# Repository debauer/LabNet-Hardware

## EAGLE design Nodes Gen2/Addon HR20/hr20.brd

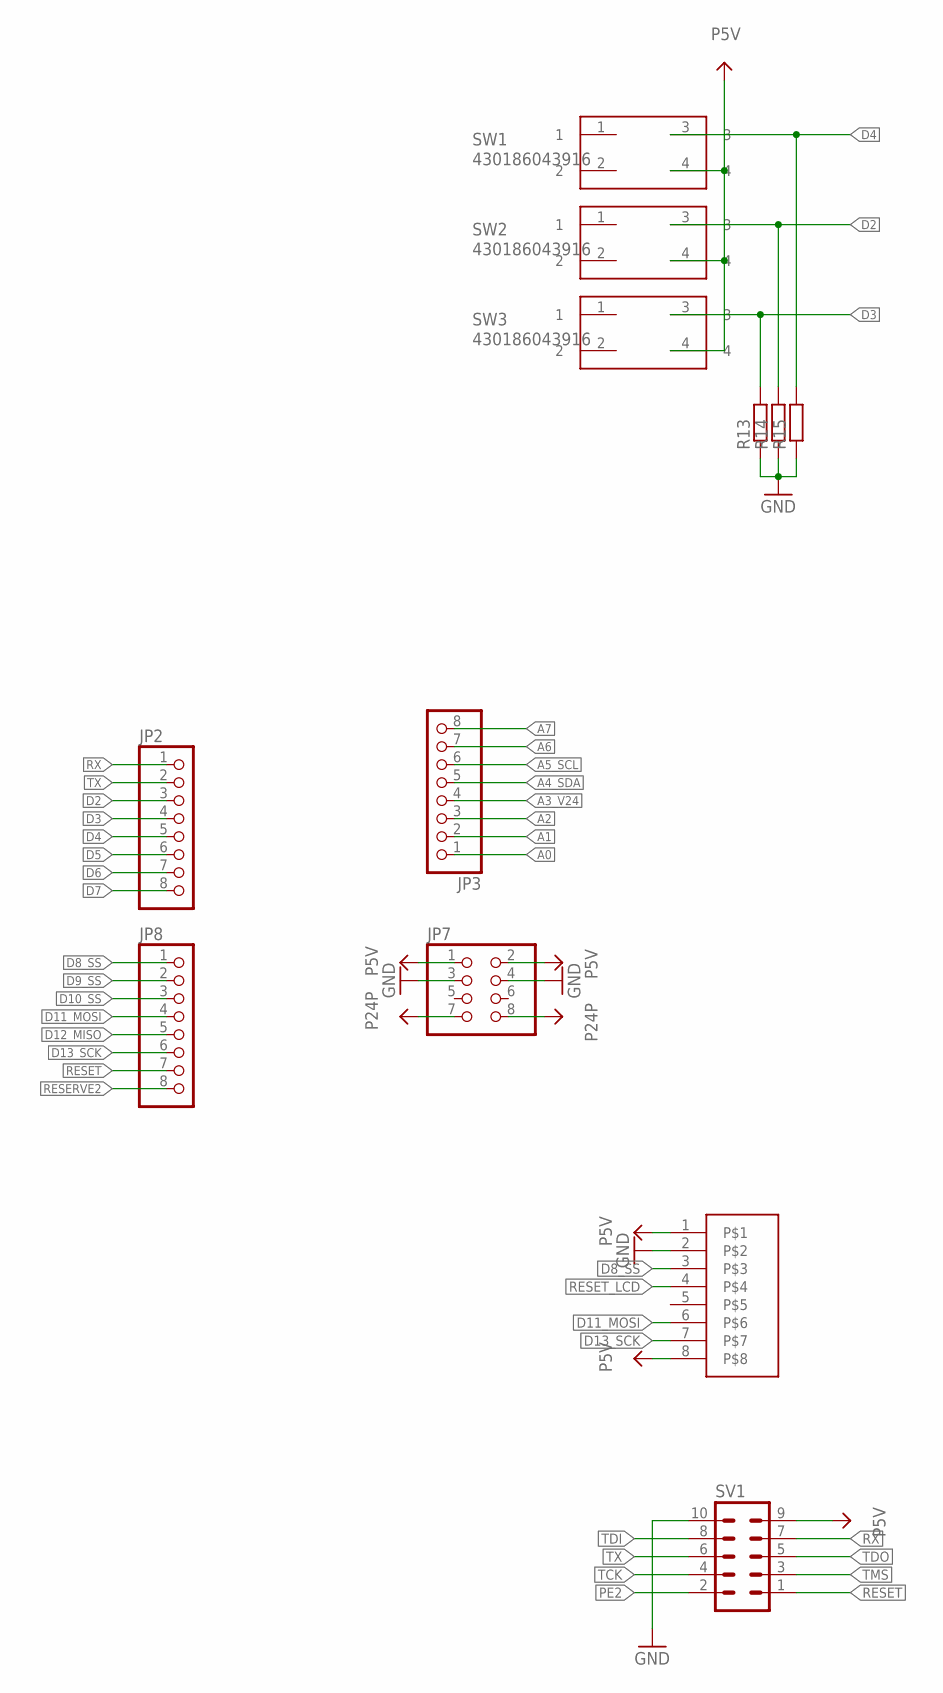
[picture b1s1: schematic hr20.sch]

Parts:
JP2, JP3, JP8: PINHD-1X8; 1X08
JP7: PINHD-2X4; 2X04
R13, R14, R15: R-EU_0207/10; 0207/10
SV1: ML10
SW1, SW2, SW3: 430186043916
U$2: 1.44-128X128

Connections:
A0: JP3.1
A1: JP3.2
A2: JP3.3
A3_V24: JP3.4
A4_SDA: JP3.5
A5_SCL: JP3.6
D2: JP2.3, R14.2, SW2.3
D3: JP2.4, R13.2, SW3.3
D4: JP2.5, R15.2, SW1.3
D5: JP2.6
D6: JP2.7
D7: JP2.8
D8_SS: JP8.1, U$2.3
D9_SS: JP8.2
D10_SS: JP8.3
D11_MOSI: JP8.4, U$2.6
D12_MISO: JP8.5
D13_SCK: JP8.6, U$2.7
GND: JP7.3, JP7.4, R13.1, R14.1, R15.1, SV1.10, U$2.2
P5V: JP7.1, JP7.2, SV1.9, SW1.4, SW2.4, SW3.4, U$2.1, U$2.8
P24P: JP7.7, JP7.8
PE2: SV1.2
RESERVE2: JP8.8
RESET: JP8.7, SV1.1
RESET_LCD: U$2.4
RX: JP2.1, SV1.7
TCK: SV1.4
TDI: SV1.8
TDO: SV1.5
TMS: SV1.3
TX: JP2.2, SV1.6

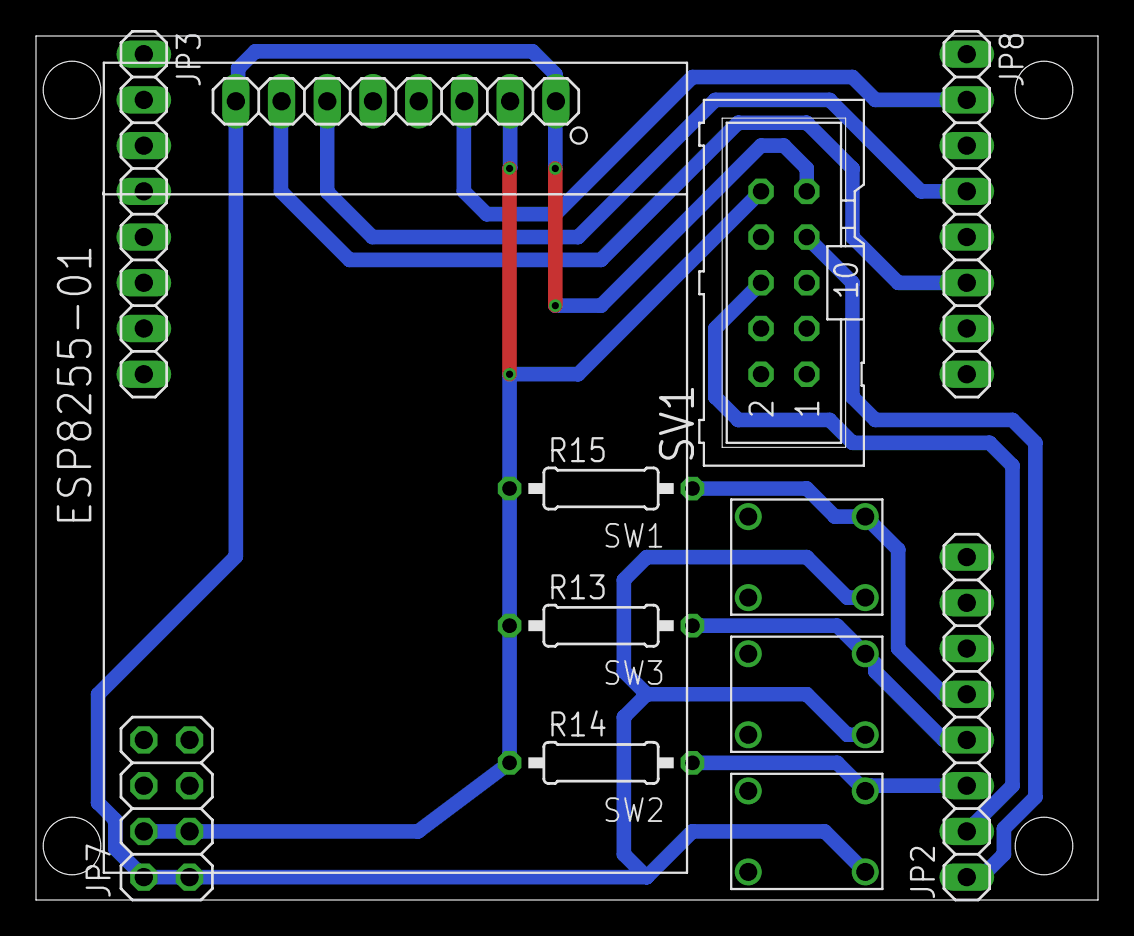
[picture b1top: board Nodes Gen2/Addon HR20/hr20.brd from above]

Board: 2 copper layers, 59.0 x 48.0 mm, 12 parts (0 on the bottom side), 12 nets.

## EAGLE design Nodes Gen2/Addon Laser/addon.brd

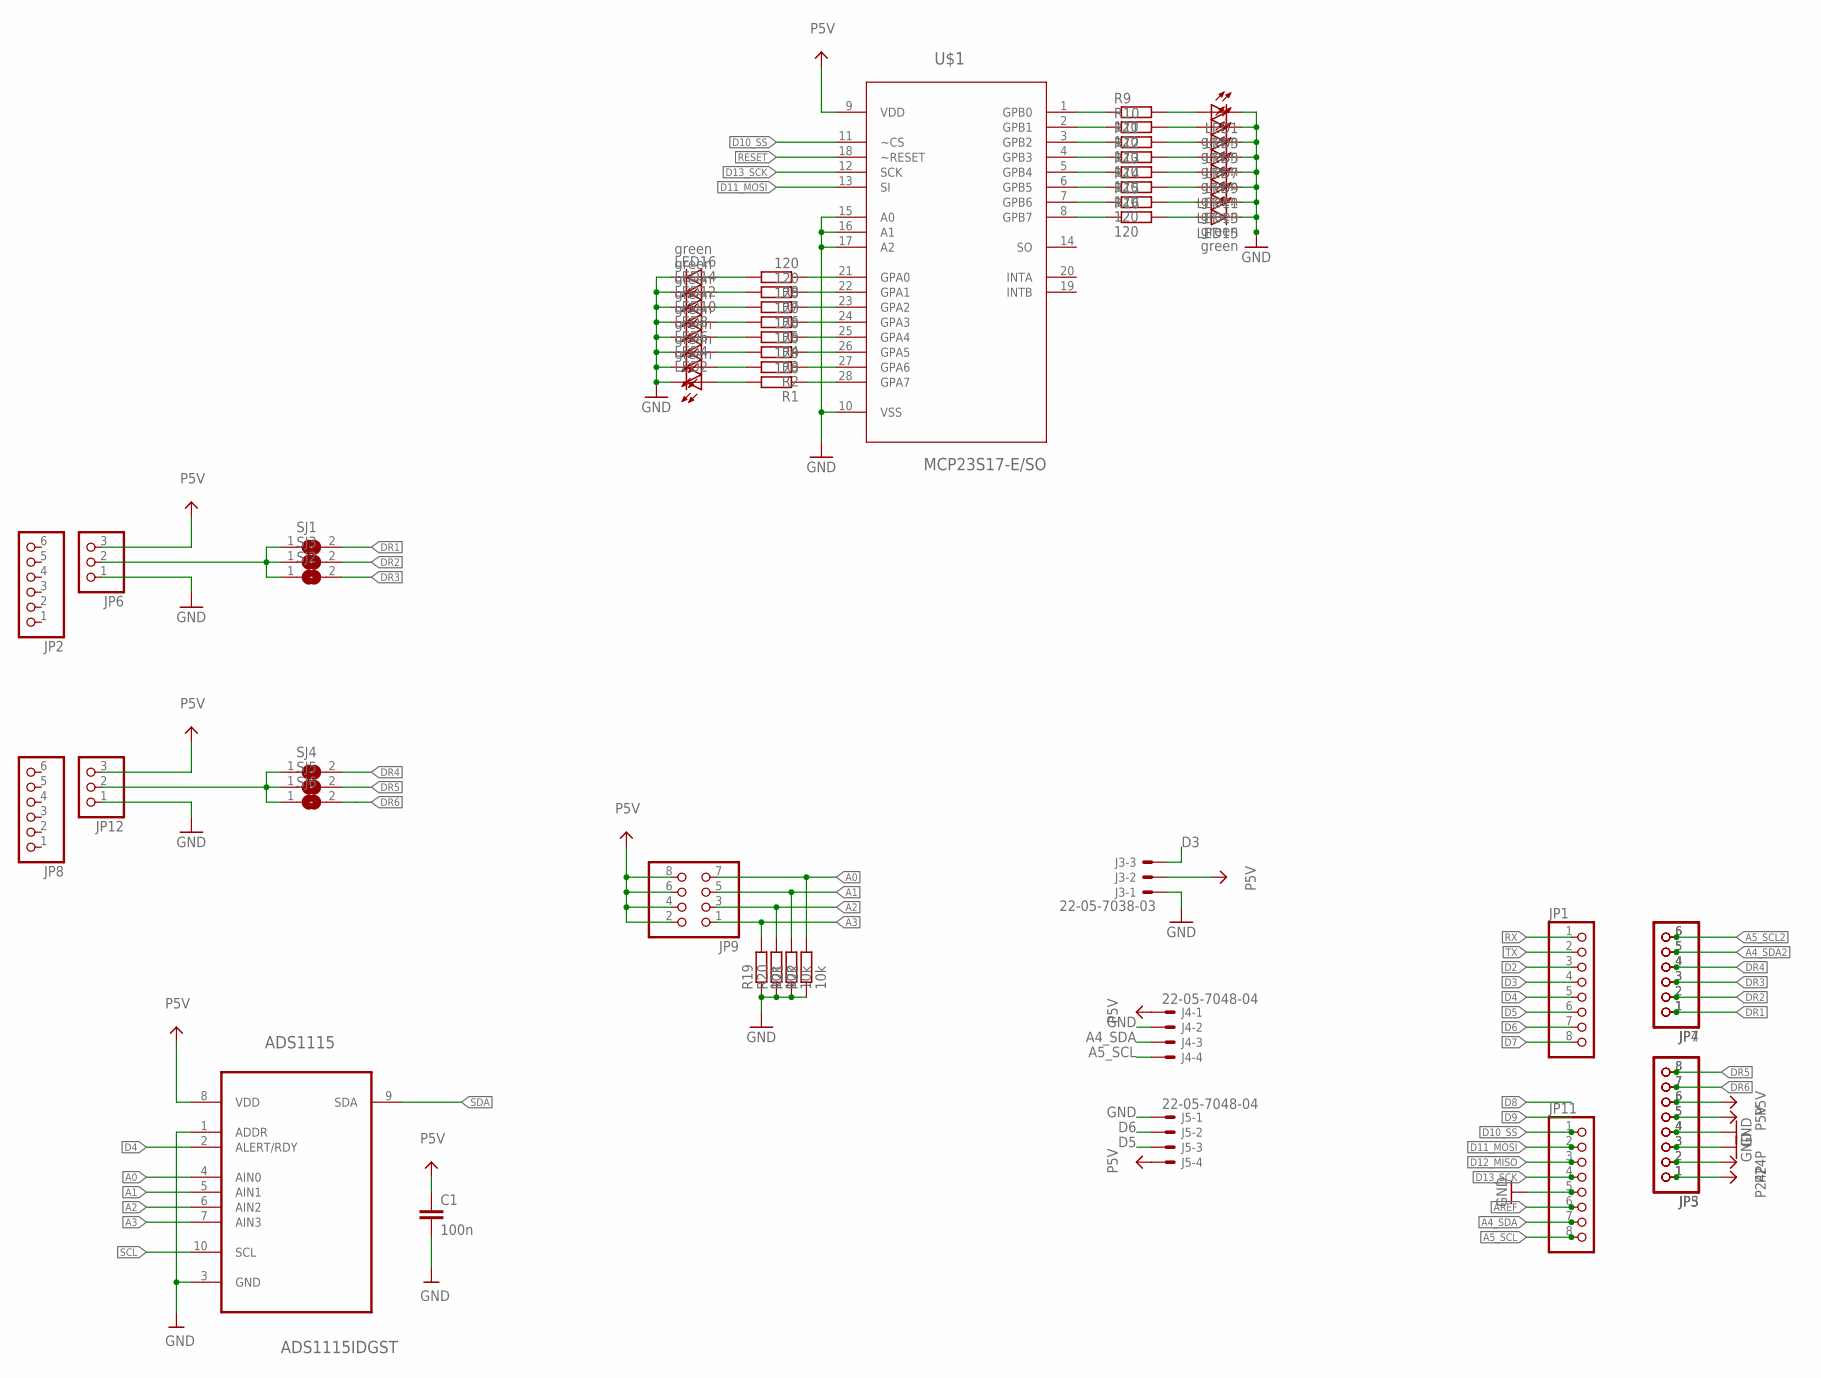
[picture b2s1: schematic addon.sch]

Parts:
ADS1115: ADS1115IDGST; SOP50P490X110-10N
C1: 100n; C0805
J3: 22-05-7038-03; 7395-03
J4, J5: 22-05-7048-04; 7395-04
JP1, JP3, JP5, JP11: PINHD-1X8; 1X08
JP2, JP4, JP7, JP8: PINHD-1X6; 1X06
JP6, JP12: PINHD-1X3; 1X03
JP9: PINHD-2X4/90; 2X04/90
LED1, LED2, LED3, LED4, LED5, LED6, LED7, LED8, LED9, LED10, LED11, LED12, LED13, LED14, LED15, LED16: green; CHIPLED_0805
R1, R2, R3, R4, R5, R6, R7, R8, R9, R10, R11, R12, R13, R14, R15, R16: 120; R0805
R19, R20, R21, R22: 10k; R0805
SJ1, SJ2, SJ3, SJ4, SJ5, SJ6: SJ
U$1: MCP23S17-E/SO; SOIC127P030X265-28N

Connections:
A0: ADS1115.4 (AIN0), JP9.7, R22.2
A1: ADS1115.5 (AIN1), JP9.5, R21.2
A2: ADS1115.6 (AIN2), JP9.3, R20.2
A3: ADS1115.7 (AIN3), JP9.1, R19.2
A4_SDA: J4.3, JP11.7
A4_SDA2: JP4.5, JP7.5
A5_SCL: J4.4, JP11.8
A5_SCL2: JP4.6, JP7.6
AREF: JP11.6
D2: JP1.3
D3: J3.3, JP1.4
D4: ADS1115.2 (ALERT/RDY), JP1.5
D5: J5.3, JP1.6
D6: J5.2, JP1.7
D7: JP1.8
D10_SS: JP11.1, U$1.11 (~CS)
D11_MOSI: JP11.2, U$1.13 (SI)
D12_MISO: JP11.3
D13_SCK: JP11.4, U$1.12 (SCK)
DR1: JP4.1, JP7.1, SJ1.2
DR2: JP4.2, JP7.2, SJ3.2
DR3: JP4.3, JP7.3, SJ2.2
DR4: JP4.4, JP7.4, SJ4.2
DR5: JP3.8, JP5.8, SJ5.2
DR6: JP3.7, JP5.7, SJ6.2
GND: ADS1115.1 (ADDR), ADS1115.3 (GND), C1.2, J3.1, J4.2, J5.1, JP3.3, JP3.4, JP5.3, JP5.4, JP6.1, JP11.5, JP12.1, LED1.C, LED2.C, LED3.C, LED4.C, LED5.C, LED6.C, LED7.C, LED8.C, LED9.C, LED10.C, LED11.C, LED12.C, LED13.C, LED14.C, LED15.C, LED16.C, R19.1, R20.1, R21.1, R22.1, U$1.10 (VSS), U$1.15 (A0), U$1.16 (A1), U$1.17 (A2)
unnamed: LED1.A, R9.2
unnamed: LED3.A, R10.2
unnamed: LED5.A, R11.2
unnamed: LED7.A, R12.2
unnamed: LED9.A, R13.2
unnamed: LED11.A, R14.2
unnamed: LED13.A, R15.2
unnamed: LED15.A, R16.2
unnamed: R9.1, U$1.1 (GPB0)
unnamed: R10.1, U$1.2 (GPB1)
unnamed: R11.1, U$1.3 (GPB2)
unnamed: R12.1, U$1.4 (GPB3)
unnamed: R13.1, U$1.5 (GPB4)
unnamed: R14.1, U$1.6 (GPB5)
unnamed: R15.1, U$1.7 (GPB6)
unnamed: R16.1, U$1.8 (GPB7)
unnamed: LED2.A, R1.2
unnamed: LED4.A, R2.2
unnamed: LED6.A, R3.2
unnamed: LED8.A, R4.2
unnamed: LED10.A, R5.2
unnamed: LED12.A, R6.2
unnamed: LED14.A, R7.2
unnamed: LED16.A, R8.2
unnamed: R1.1, U$1.28 (GPA7)
unnamed: R2.1, U$1.27 (GPA6)
unnamed: R3.1, U$1.26 (GPA5)
unnamed: R4.1, U$1.25 (GPA4)
unnamed: R5.1, U$1.24 (GPA3)
unnamed: R6.1, U$1.23 (GPA2)
unnamed: R7.1, U$1.22 (GPA1)
unnamed: R8.1, U$1.21 (GPA0)
unnamed: JP6.2, SJ1.1, SJ2.1, SJ3.1
unnamed: JP12.2, SJ4.1, SJ5.1, SJ6.1
P5V: ADS1115.8 (VDD), C1.1, J3.2, J4.1, J5.4, JP3.5, JP3.6, JP5.5, JP5.6, JP6.3, JP9.2, JP9.4, JP9.6, JP9.8, JP12.3, U$1.9 (VDD)
P24P: JP3.1, JP3.2, JP5.1, JP5.2
RESET: U$1.18 (~RESET)
RX: JP1.1
SCL: ADS1115.10 (SCL)
SDA: ADS1115.9 (SDA)
TX: JP1.2

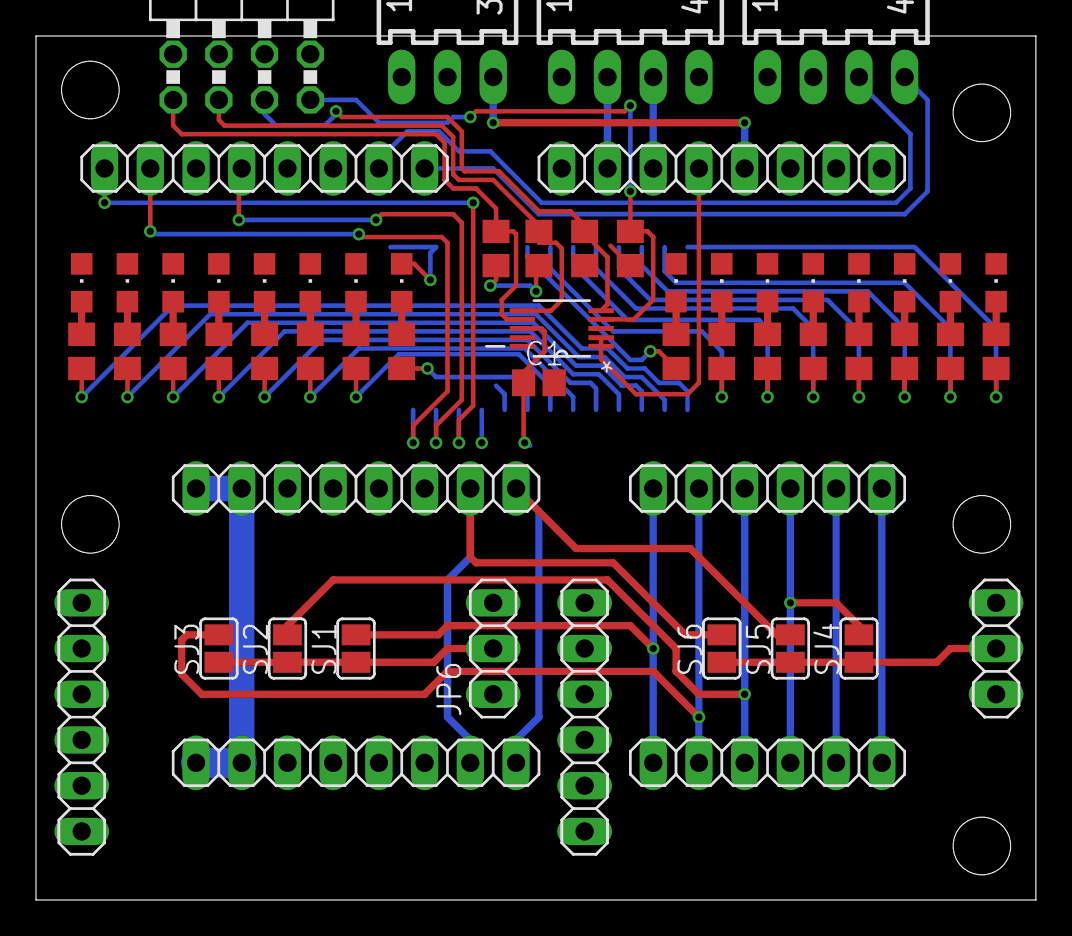
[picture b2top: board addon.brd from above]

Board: 2 copper layers, 55.5 x 48.0 mm, 59 parts (1 on the bottom side), 58 nets.

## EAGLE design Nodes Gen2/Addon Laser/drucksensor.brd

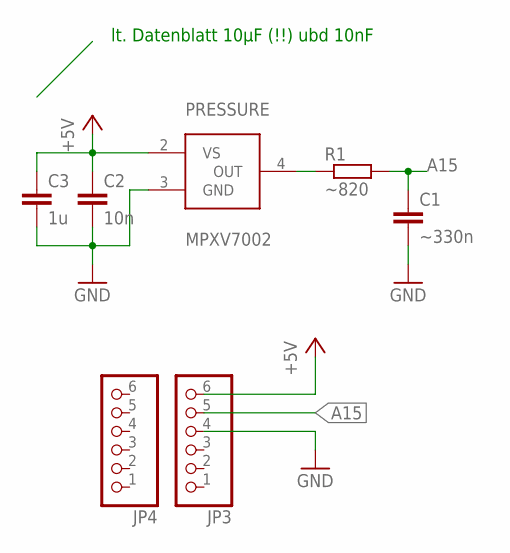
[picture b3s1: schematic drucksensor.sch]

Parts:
C1: ~330n; C0805
C2: 10n; C0805
C3: 1u; C0805
JP3, JP4: PINHD-1X6; 1X06
PRESSURE: MPXV7002; MPXV7002DP
R1: ~820; R0805

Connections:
+5V: C2.1, C3.1, JP3.6, PRESSURE.2 (VS)
A15: C1.1, JP3.5, R1.2
GND: C1.2, C2.2, C3.2, JP3.4, PRESSURE.3 (GND)
unnamed: PRESSURE.4 (OUT), R1.1

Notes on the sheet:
lt. Datenblatt 10µF (!!) ubd 10nF

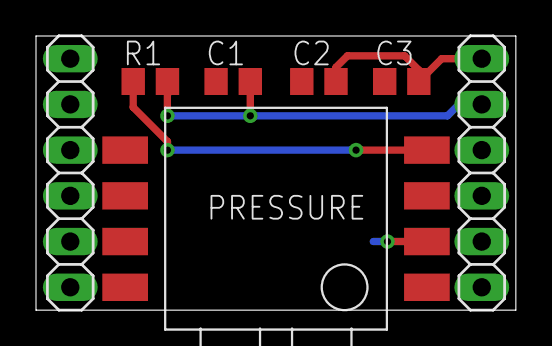
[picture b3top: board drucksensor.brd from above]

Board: 2 copper layers, 26.7 x 15.2 mm, 7 parts (0 on the bottom side), 4 nets.

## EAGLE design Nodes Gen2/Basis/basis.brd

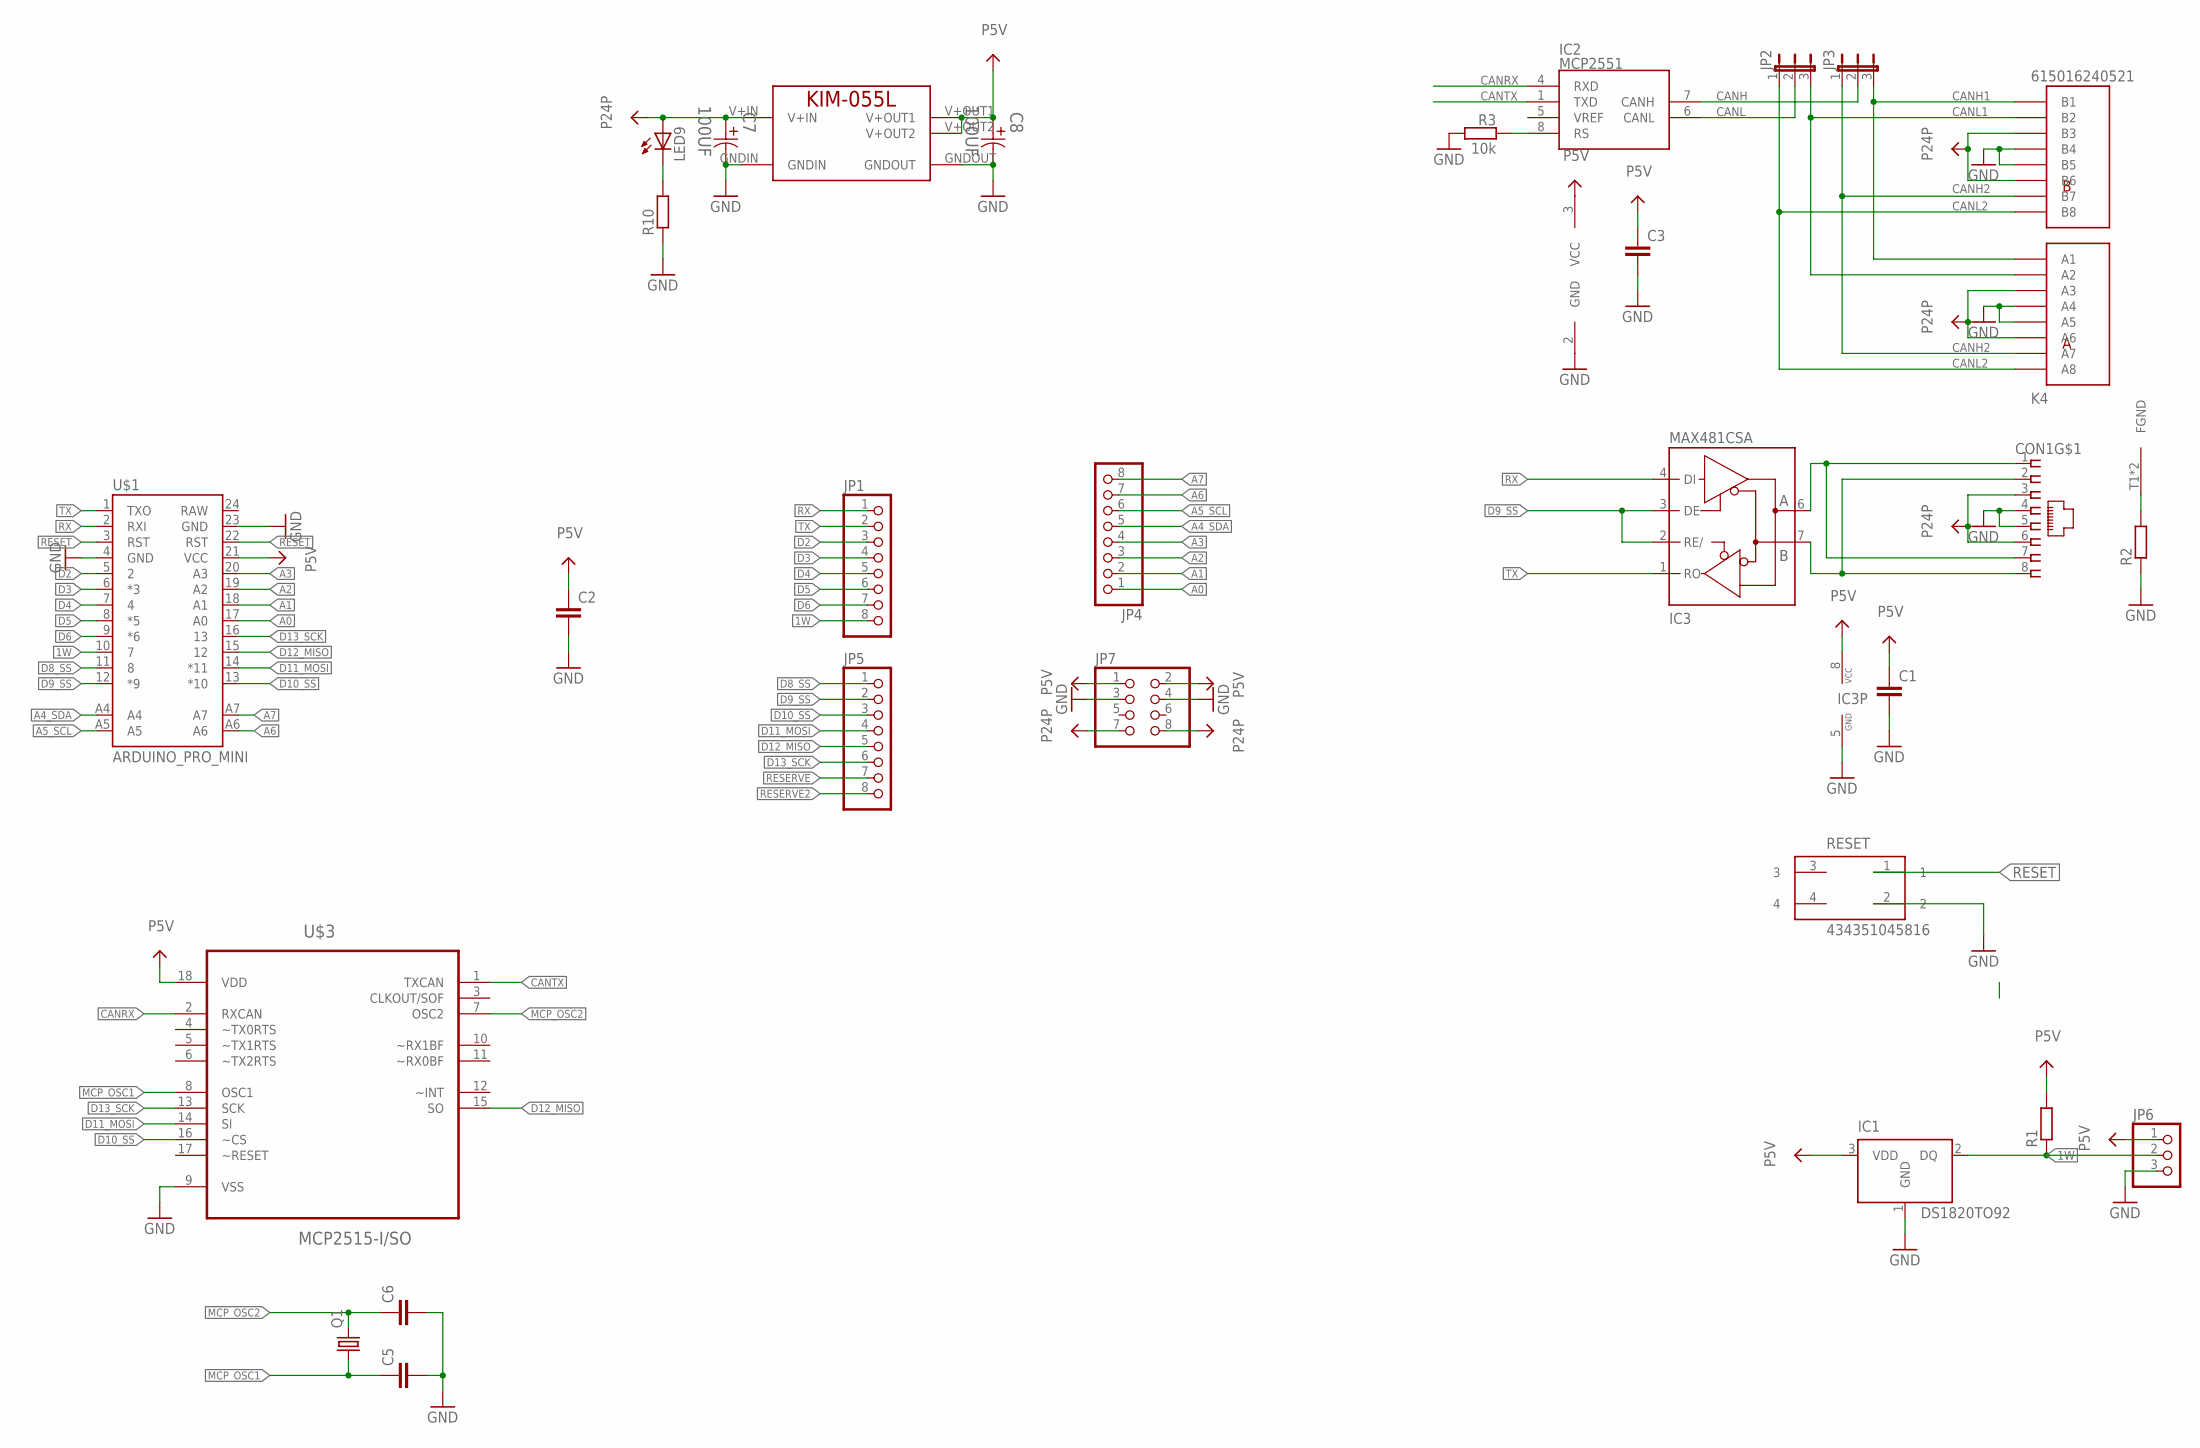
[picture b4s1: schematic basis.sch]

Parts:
C1, C2, C3, C5, C6: C-EUC0805; C0805
C7, C8: 100UF; CAPAE830X1050N
CON1: MEBP_8-8G; MEBP
IC1: DS1820TO92; TO-92
IC2: MCP2551; SO-8
IC3: MAX481CSA; SO08
JP1, JP4, JP5: PINHD-1X8; 1X08
JP2, JP3: JP2E; JP2
JP6: PINHD-1X3/90; 1X03/90
JP7: PINHD-2X4; 2X04
K4: 615016240521
LED9: LED3MM
MOD1: KIM-055L
Q1: CRYSTALHC49S; HC49/S
R1: R-EU_M0805; M0805
R2, R10: R-EU_R0805; R0805
R3: 10k; R0603
RESET: 434351045816
U$1: ARDUINO_PRO_MINI
U$3: MCP2515-I/SO; SOIC127P1034X264-18N

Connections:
1W: IC1.2 (DQ), JP1.8, JP6.2, R1.1, U$1.10 (7)
A0: JP4.1, U$1.17 (A0)
A1: JP4.2, U$1.18 (A1)
A2: JP4.3, U$1.19 (A2)
A3: JP4.4, U$1.20 (A3)
A4_SDA: JP4.5, U$1.A4
A5_SCL: JP4.6, U$1.A5
A6: U$1.A6
A7: U$1.A7
CANH: IC2.7 (CANH), JP3.2
CANH1: JP3.3, K4.A1, K4.B1
CANH2: JP3.1, K4.A7, K4.B7
CANL: IC2.6 (CANL), JP2.2
CANL1: JP2.3, K4.A2, K4.B2
CANL2: JP2.1, K4.A8, K4.B8
CANRX: IC2.4 (RXD), U$3.2 (RXCAN)
CANTX: IC2.1 (TXD), U$3.1 (TXCAN)
D2: JP1.3, U$1.5 (2)
D3: JP1.4, U$1.6 (*3)
D4: JP1.5, U$1.7 (4)
D5: JP1.6, U$1.8 (*5)
D6: JP1.7, U$1.9 (*6)
D8_SS: JP5.1, U$1.11 (8)
D9_SS: IC3.2 (RE/), IC3.3 (DE), JP5.2, U$1.12 (*9)
D10_SS: JP5.3, U$1.13 (*10), U$3.16 (~CS)
D11_MOSI: JP5.4, U$1.14 (*11), U$3.14 (SI)
D12_MISO: JP5.5, U$1.15 (12), U$3.15 (SO)
D13_SCK: JP5.6, U$1.16 (13), U$3.13 (SCK)
GND: C1.2, C2.2, C3.2, C5.2, C6.2, C7.2, C8.2, CON1.4, CON1.5, IC1.1 (GND), IC2.2 (GND), IC3.5 (GND), JP6.3, JP7.3, JP7.4, K4.A4, K4.A5, K4.B4, K4.B5, MOD1.GNDIN, MOD1.GNDOUT, R2.1, R3.2, R10.1, RESET.2, U$1.4 (GND), U$1.23 (GND), U$3.9 (VSS)
MCP_OSC1: C5.1, Q1.1, U$3.8 (OSC1)
MCP_OSC2: C6.1, Q1.2, U$3.7 (OSC2)
unnamed: IC2.8 (RS), R3.1
unnamed: CON1.T1 (FGND), CON1.T2 (FGND), R2.2
unnamed: LED9.K (C), R10.2
P5V: C1.1, C2.1, C3.1, C8.1, IC1.3 (VDD), IC2.3 (VCC), IC3.8 (VCC), JP6.1, JP7.1, JP7.2, MOD1.V+OUT1, MOD1.V+OUT2, R1.2, U$1.21 (VCC), U$3.18 (VDD)
P24P: C7.1, CON1.3, CON1.6, JP7.7, JP7.8, K4.A3, K4.A6, K4.B3, K4.B6, LED9.A, MOD1.V+IN
RESERVE: JP5.7
RESERVE2: JP5.8
RESET: RESET.1, U$1.3 (RST), U$1.22 (RST)
RS485_A: CON1.1, CON1.7, IC3.6 (A)
RS485_B: CON1.2, CON1.8, IC3.7 (B)
RX: IC3.4 (DI), JP1.1, U$1.2 (RXI)
TX: IC3.1 (RO), JP1.2, U$1.1 (TXO)

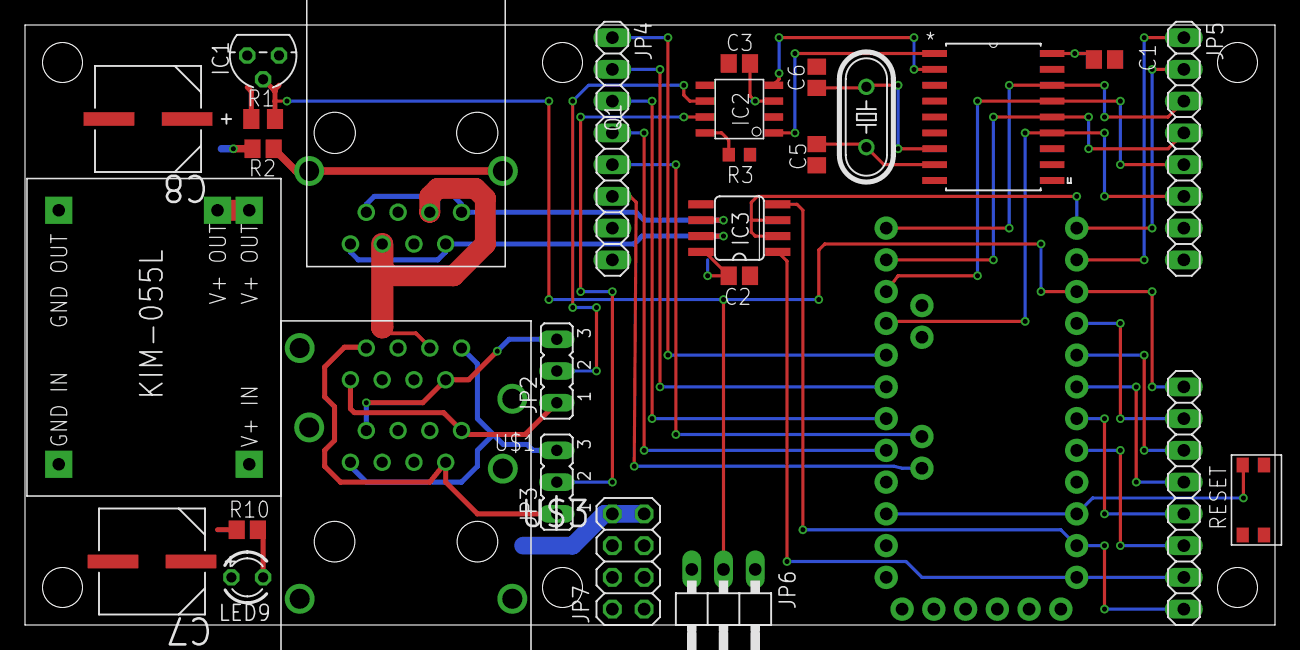
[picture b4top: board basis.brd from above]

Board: 2 copper layers, 100.0 x 48.0 mm, 29 parts (0 on the bottom side), 39 nets.

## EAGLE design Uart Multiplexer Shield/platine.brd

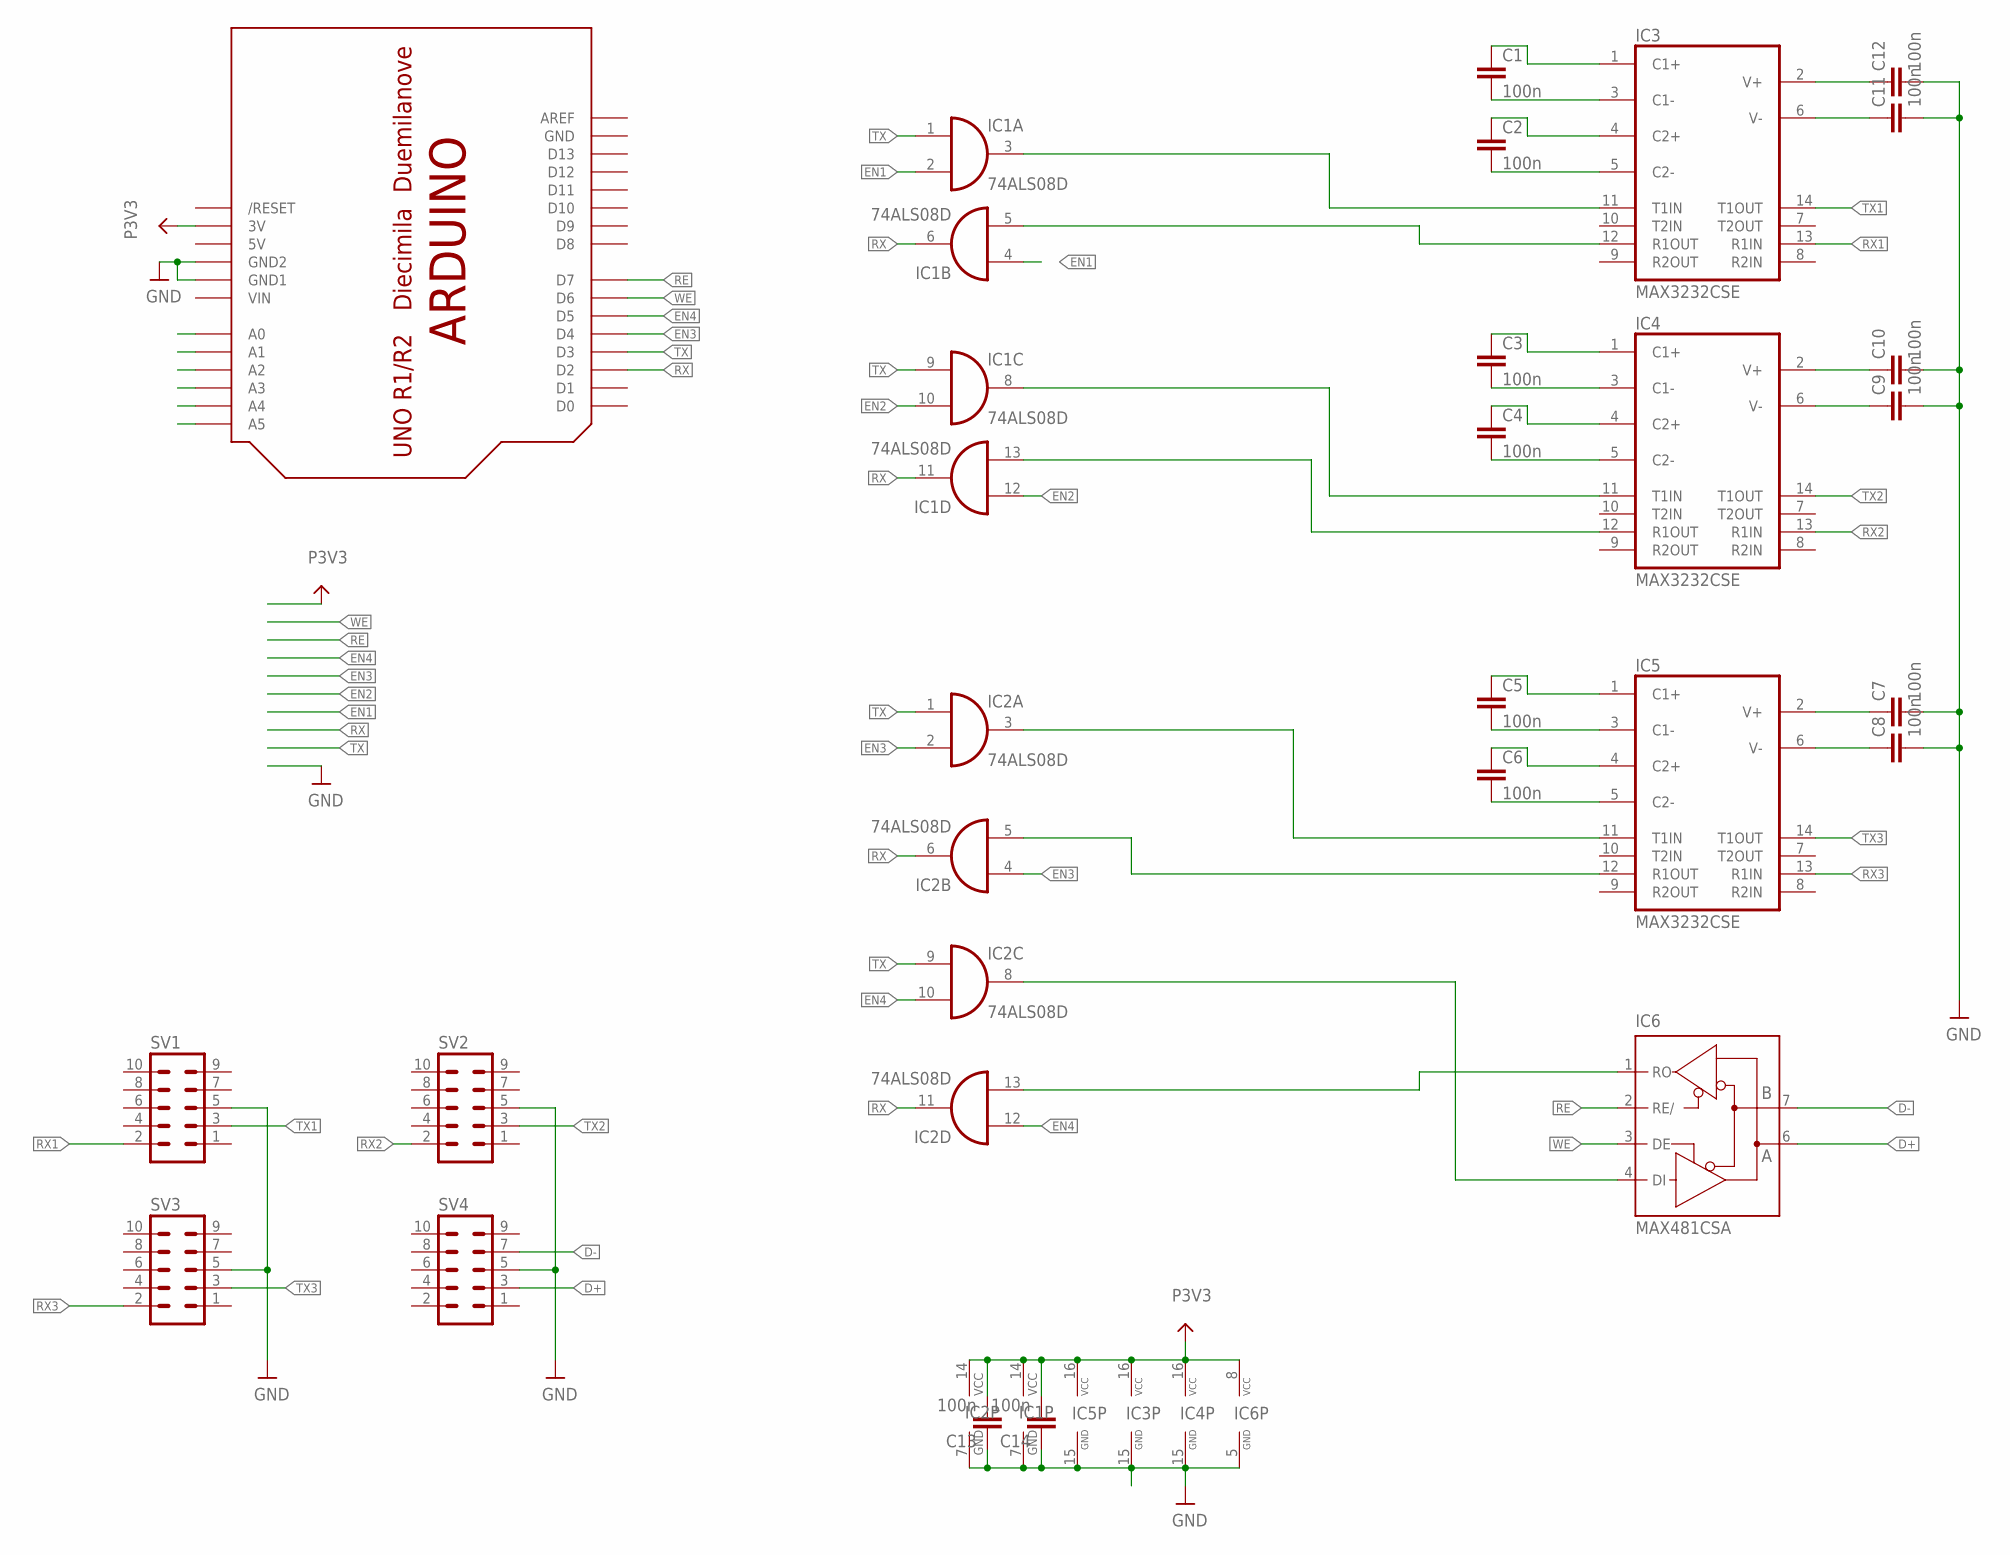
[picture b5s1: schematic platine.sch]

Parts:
C1, C2, C3, C4, C5, C6, C7, C8, C9, C10, C11, C12, C13, C14: 100n; C1210
IC1, IC2: 74ALS08D; SO14
IC3, IC4, IC5: MAX3232CSE; SO16
IC6: MAX481CSA; SO08
SV1, SV2, SV3, SV4: ML10
U$1: ARDUINO-NOHOLE

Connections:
5V: U$1.5V
D+: IC6.6 (A), SV4.3
D-: IC6.7 (B), SV4.7
EN1: IC1.2 (I1), IC1.4 (I0), U$1.A0
EN2: IC1.10 (I1), IC1.12 (I0), U$1.A1
EN3: IC2.2 (I1), IC2.4 (I0), U$1.D4
EN4: IC2.10 (I1), IC2.12 (I0), U$1.D5
GND: C7.2, C8.2, C9.2, C10.2, C11.2, C12.2, C13.1, C14.1, IC1.7 (GND), IC2.7 (GND), IC3.15 (GND), IC4.15 (GND), IC5.15 (GND), IC6.5 (GND), SV1.5, SV2.5, SV3.5, SV4.5, U$1.GND, U$1.GND1, U$1.GND2
unnamed: IC1.5 (I1), IC3.12 (R1OUT)
unnamed: IC1.3 (O), IC3.11 (T1IN)
unnamed: IC1.8 (O), IC4.11 (T1IN)
unnamed: IC1.13 (I1), IC4.12 (R1OUT)
unnamed: IC2.3 (O), IC5.11 (T1IN)
unnamed: IC2.5 (I1), IC5.12 (R1OUT)
unnamed: IC2.8 (O), IC6.4 (DI)
unnamed: IC2.13 (I1), IC6.1 (RO)
unnamed: C6.2, IC5.5 (C2-)
unnamed: C6.1, IC5.4 (C2+)
unnamed: C5.2, IC5.3 (C1-)
unnamed: C5.1, IC5.1 (C1+)
unnamed: C4.2, IC4.5 (C2-)
unnamed: C4.1, IC4.4 (C2+)
unnamed: C3.1, IC4.1 (C1+)
unnamed: C3.2, IC4.3 (C1-)
unnamed: C2.2, IC3.5 (C2-)
unnamed: C2.1, IC3.4 (C2+)
unnamed: C1.2, IC3.3 (C1-)
unnamed: C1.1, IC3.1 (C1+)
unnamed: C12.1, IC3.2 (V+)
unnamed: C11.1, IC3.6 (V-)
unnamed: C7.1, IC5.2 (V+)
unnamed: C8.1, IC5.6 (V-)
unnamed: C10.1, IC4.2 (V+)
unnamed: C9.1, IC4.6 (V-)
P3V3: C13.2, C14.2, IC1.14 (VCC), IC2.14 (VCC), IC3.16 (VCC), IC4.16 (VCC), IC5.16 (VCC), IC6.8 (VCC), U$1.3V
RE: IC6.2 (RE/), U$1.D7
RX: IC1.6 (O), IC1.11 (O), IC2.6 (O), IC2.11 (O), U$1.D2
RX1: IC3.13 (R1IN), SV1.2
RX2: IC4.13 (R1IN), SV2.2
RX3: IC5.13 (R1IN), SV3.2
TX: IC1.1 (I0), IC1.9 (I0), IC2.1 (I0), IC2.9 (I0), U$1.D3
TX1: IC3.14 (T1OUT), SV1.3
TX2: IC4.14 (T1OUT), SV2.3
TX3: IC5.14 (T1OUT), SV3.3
VIN: U$1.VIN
WE: IC6.3 (DE), U$1.D6

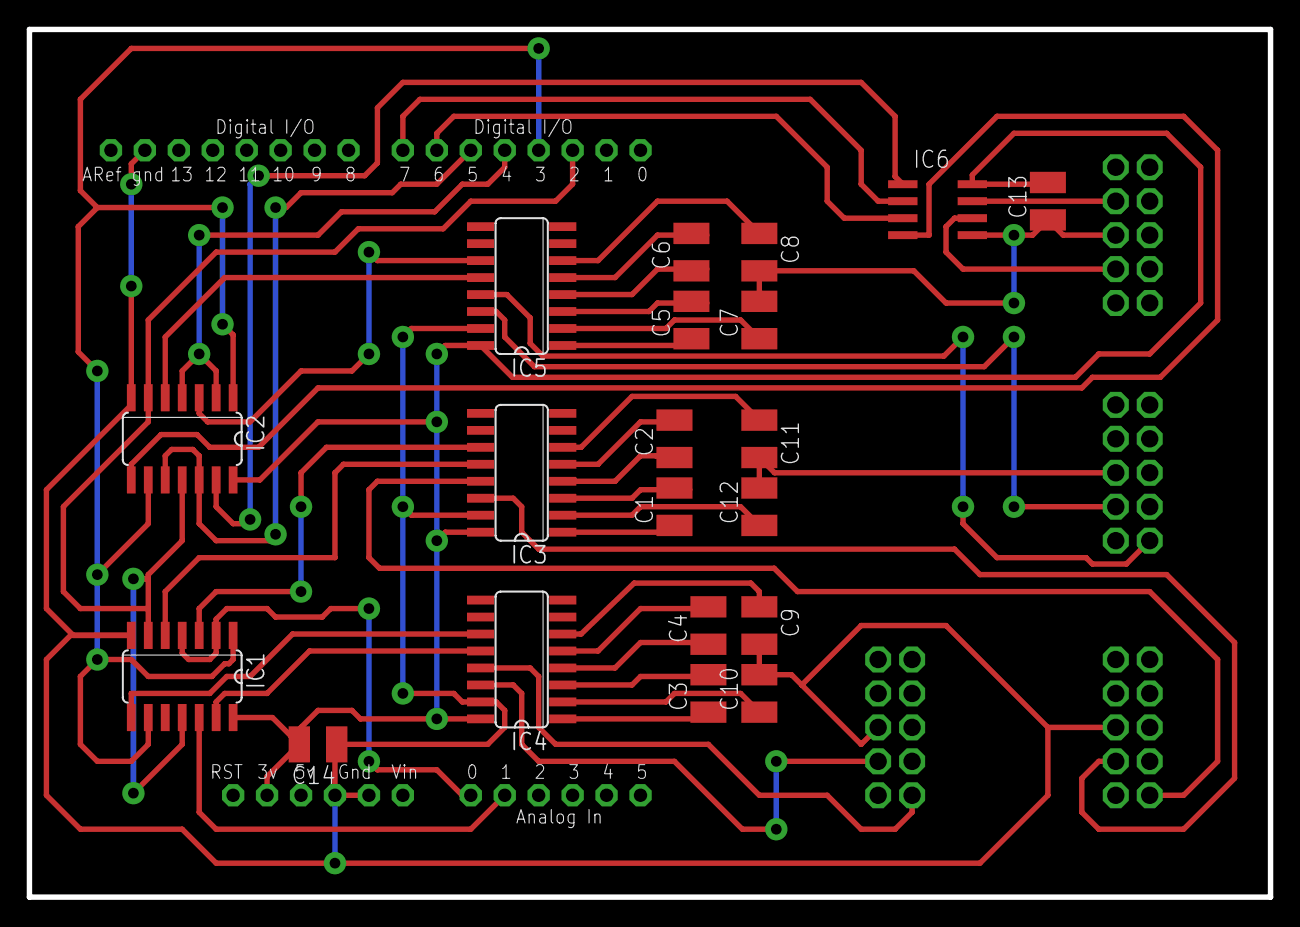
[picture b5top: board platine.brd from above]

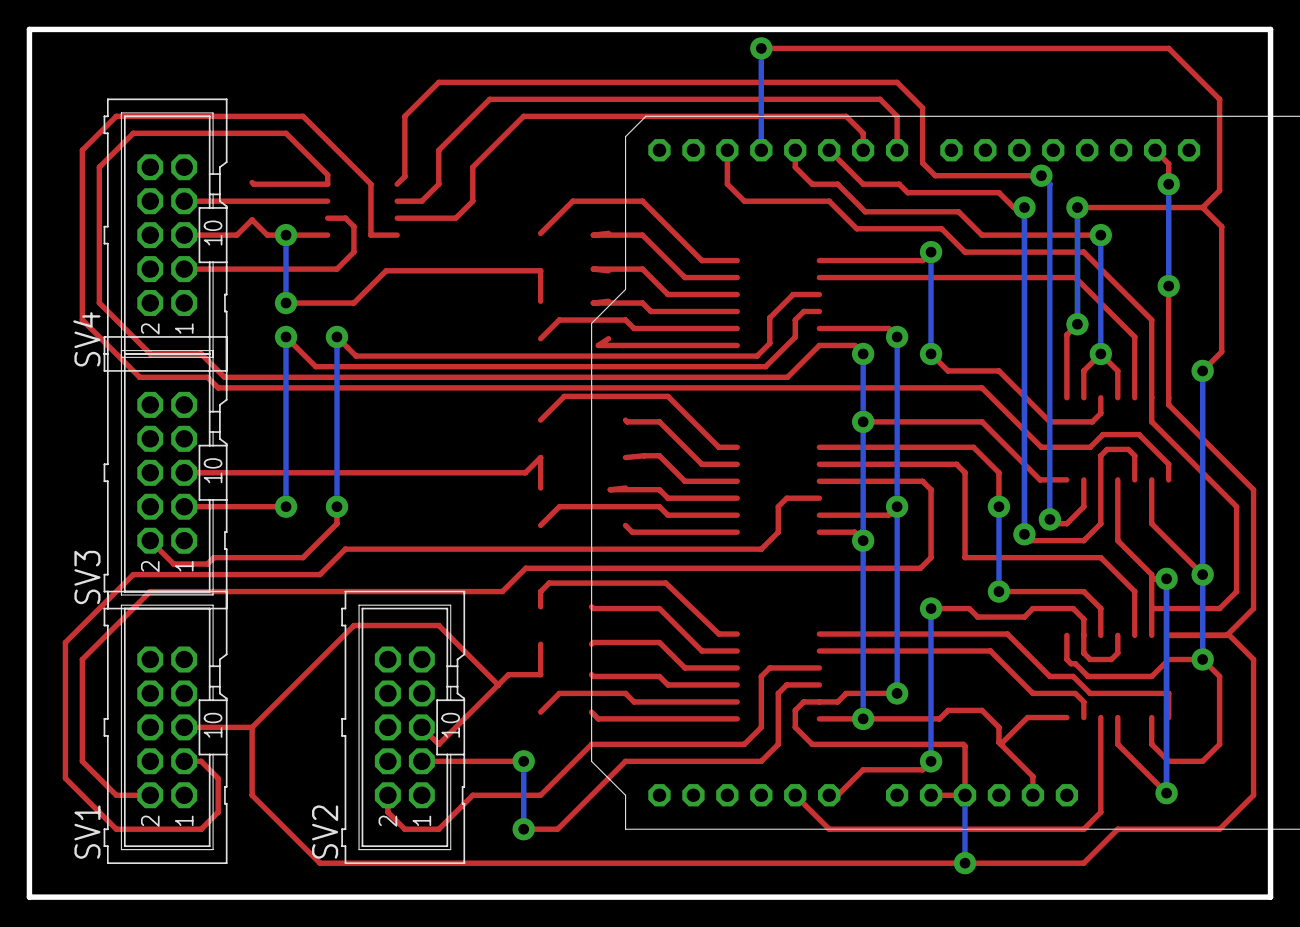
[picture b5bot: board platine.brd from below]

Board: 2 copper layers, 92.9 x 64.9 mm, 25 parts (4 on the bottom side), 44 nets.

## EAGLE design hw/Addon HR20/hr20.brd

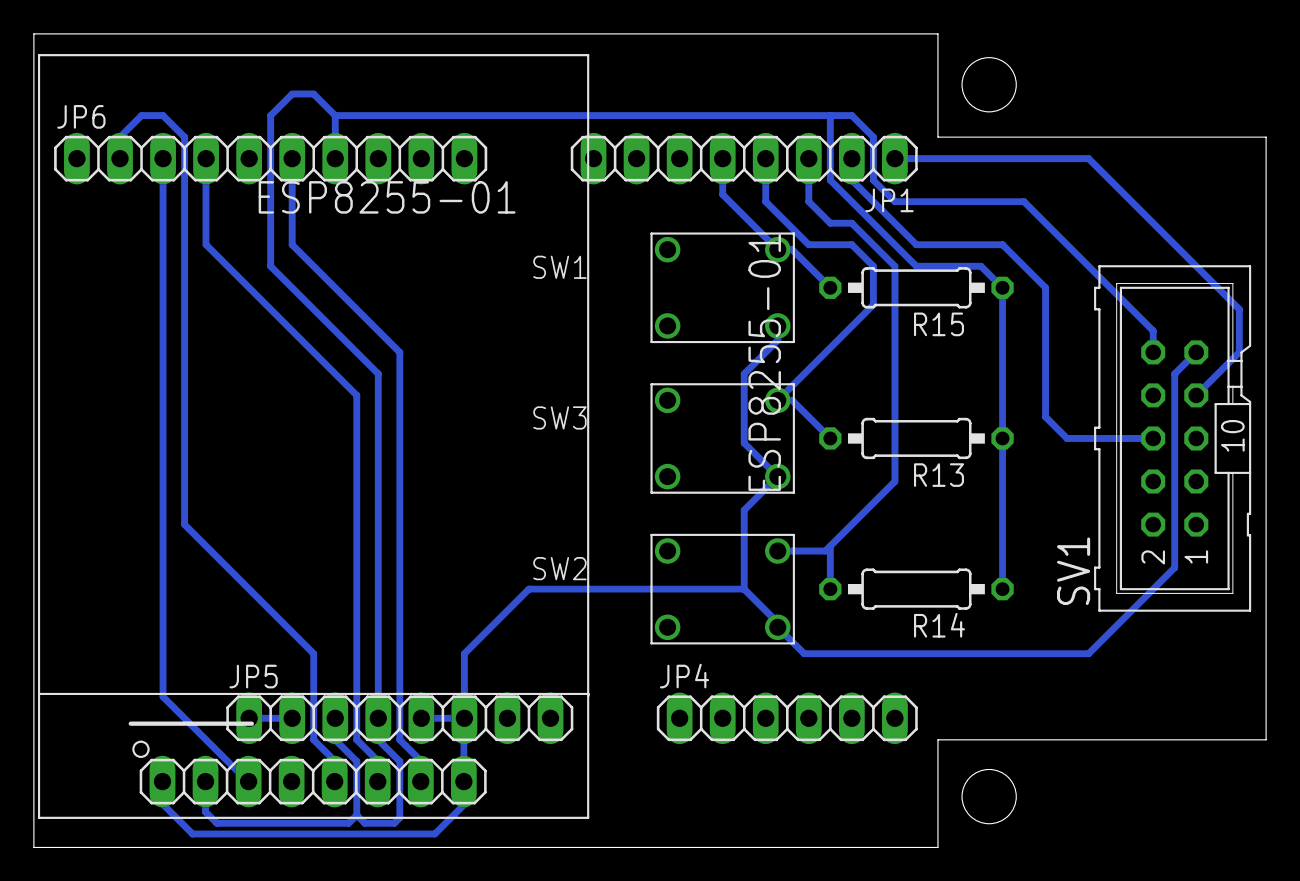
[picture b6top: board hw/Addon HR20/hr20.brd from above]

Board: 2 copper layers, 72.7 x 48.0 mm, 12 parts (0 on the bottom side), 12 nets.

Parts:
JP1, JP5: 1X08
JP4: 1X06
JP6: 1X10
R13, R14, R15: 0207/10
SV1: ML10
SW1, SW2, SW3: 430186043916
U$2: 1.44-128X128

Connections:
D2: JP1.3, R14.2, SW2.3
D3: JP1.4, R13.2, SW3.3
D4: JP1.5, R15.2, SW1.3
D9: JP6.2, U$2.5
D10_SS: JP6.3, U$2.3
D11_MOSI: JP6.4, U$2.6
D13_SCK: JP6.6, U$2.7
GND: JP5.3, JP5.4, JP6.7, R13.1, R14.1, R15.1, SV1.10, U$2.2
P5V: JP5.5, JP5.6, SV1.9, SW1.4, SW2.4, SW3.4, U$2.1, U$2.8
P24P: JP5.1, JP5.2
RX: JP1.1, SV1.7
TX: JP1.2, SV1.6

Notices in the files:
parts and their libraries:
Wuerth_Elektronik_Switch: Copyright: Würth Elektronik
SparkFun-Boards: Licensing: Creative Commons ShareAlike 4.0 International - https://creativecommons.org/licenses/by-sa/4.0
